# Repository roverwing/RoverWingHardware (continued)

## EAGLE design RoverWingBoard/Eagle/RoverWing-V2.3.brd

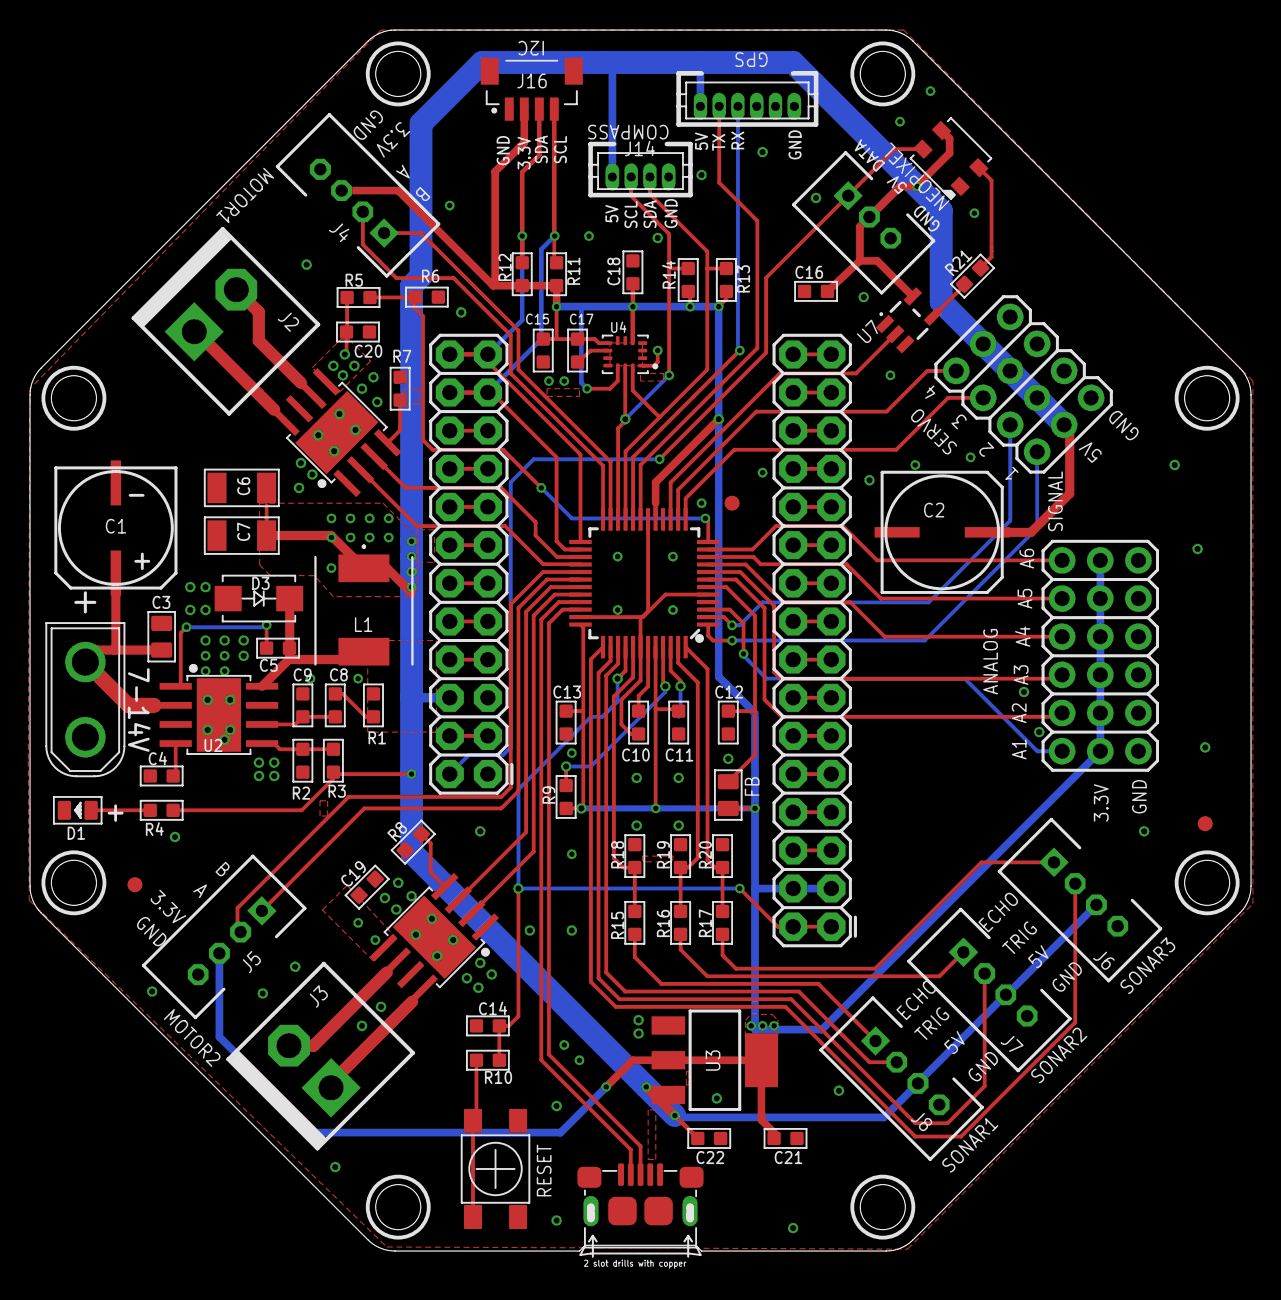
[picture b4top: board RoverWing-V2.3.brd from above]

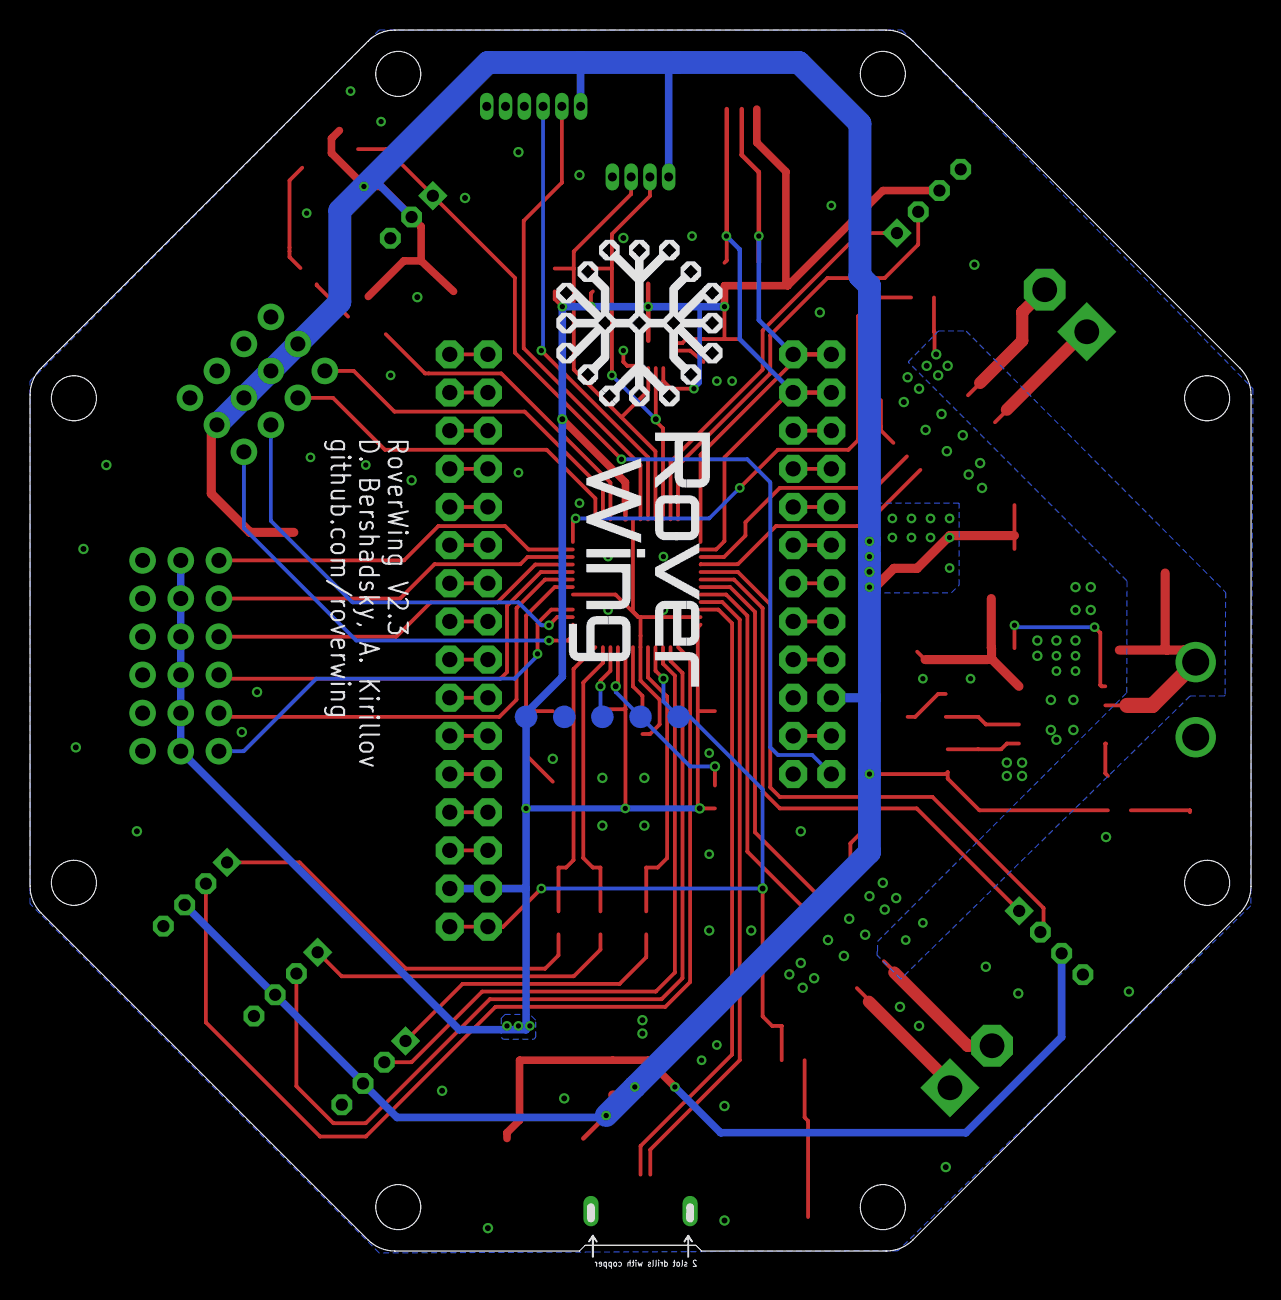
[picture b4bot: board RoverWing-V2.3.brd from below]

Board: 2 copper layers, 81.3 x 81.3 mm, 91 parts (5 on the bottom side), 84 nets.

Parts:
C1, C2: 220uF; CAP-8X10.5
C3: 10uF; 0805
C4, C18: 10nF; 0603
C5, C11, C12, C13, C14, C15, C16, C19, C20: 100nF; 0603
C6, C7: 47uF; 1206
C8, C17: 2.2nF; 0603
C9: 22pF; 0603
C10, C21, C22: 1uF; 0603
D1: GREEN; LED-0805
D2: LED3535
D3: CDBA540-HF; SMA-DO214AC
FB: 330R-1500MA; 0805
FRAME1, FRAME2: FRAME-LETTERNO_PACKAGE; DUMMY
J1: XT30UPB-M
J2, J3: HEADER-VH; B2P-VH
J4, J5, J6, J7, J8: HEADER-PH-4P; B4B-PH-K
J9: HEADER-PH-3P; B3B-PH-K
J10: HEADER-3X04; 3X04
J11: HEADER-3X06ANGLE; 3X06
J12: HEADER-2X16; 2X16
J13: HEADER-2X12; 2X12
J14: DF13-4P-1.25DSA
J15: DF13-6P-1.25DSA
J16: HEADER-SH-4P; CONN_BM04B-SRSS-TB(LF)(SN)
L1: 4.7uH; IND_TDK_7.1X6.5
R1, R5: 37.4K; 0603
R2, R11, R12, R13, R14, R18, R19, R20: 1.8K; 0603
R3, R6: 9.53K; 0603
R4, R9, R10, R15, R16, R17: 1K; 0603
R7, R8: 22K; 0603
R21: 330; 0603
SW1: SW-TACTILE-4.5X4.5_SMD; TL3305
TP1, TP2, TP3, TP4, TP5: TPTP15R; TP15R
U1: ATSAMD21G; TQFP-48-EDITED
U2: TPS54531; HSOP8
U3: PMIC-AZ1117EH-3.3; SOT223
U4: ICM-42605; PQFN50P300X250X97-14N
U5, U6: DRV8871; HSOP8
U7: 74AHCT1G125DBV; SOT23-5
U$3, U$4, U$14, U$15, U$24, U$25, U$26, U$27: MOUNTINGHOLE3.0_NPH; MOUNTINGHOLE_3.0_NPH
U$11, U$13, U$17: FIDUCIAL; FIDUCIAL_1MM
USB1: MICRO-USB-SMD-B-(10118193-0001LF); MICRO-USB5+6P-SMD-0.65-B

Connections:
3.3V: C11.2, C13.2, C15.2, C17.2, C18.1, C21.2, FB.2, J4.3, J5.3, J11.2, J11.5, J11.8, J11.11, J11.14, J11.17, J12.3, J12.4, J16.2, R9.1, R11.1, R12.1, R13.1, R14.1, TP5.TP, U1.17, U1.36, U1.44, U3.2, U3.4, U4.5, U4.8, U4.12
5V: C2.+, C6.2, C7.2, C16.2, C22.2, D2.3, J6.3, J7.3, J8.3, J9.2, J10.2, J10.5, J10.8, J10.11, J13.6, J14.P$1, J15.P$1, L1.1, R3.2, R4.2, U3.3, U7.5
12V: C1.+, C3.2, C19.1, C20.1, J1.+, R5.2, U2.2, U5.5, U6.5
!RESET: C14.1, J12.1, J12.2, R10.2, TP1.TP, U1.40
ANALOG1: J11.3, U1.3
ANALOG2: J11.6, U1.7
ANALOG3: J11.9, U1.8
ANALOG4: J11.12, U1.9
ANALOG5: J11.15, U1.10
ANALOG6: J11.18, U1.11
BOOT: C5.1, U2.1
D+: U1.34, USB1.3
D-: U1.33, USB1.2
ENC1A: J4.2, U1.24
ENC1B: J4.1, U1.23
ENC2A: J5.2, U1.29
ENC2B: J5.1, U1.30
GND: C1.-, C2.-, C3.1, C4.1, C6.1, C7.1, C9.1, C10.1, C11.1, C12.1, C13.1, C14.2, C15.1, C16.1, C17.1, C18.2, C19.2, C20.2, C21.1, C22.1, D1.-, D2.1, D3.A, J1.-, J4.4, J5.4, J6.4, J7.4, J8.4, J9.3, J10.1, J10.4, J10.7, J10.10, J11.1, J11.4, J11.7, J11.10, J11.13, J11.16, J12.7, J12.8, J14.P$4, J15.P$6, J16.1, R1.1, R2.1, R6.2, R7.2, R8.2, R18.2, R19.2, R20.2, SW1.2, SW1.3, TP4.TP, U1.5, U1.18, U1.35, U1.42, U2.7, U2.GND, U2.P$1, U2.P$2, U2.P$3, U2.P$4, U3.1, U4.1, U4.6, U4.7, U4.9, U5.1, U5.7, U5.GND, U5.P$1, U5.P$2, U5.P$3, U5.P$4, U6.1, U6.7, U6.GND, U6.P$1, U6.P$2, U6.P$3, U6.P$4, U7.1, U7.3, USB1.5, USB1.S1, USB1.S2, USB1.S3, USB1.S4, USB1.S5, USB1.S6
MOTOR1A: U1.27, U5.3
MOTOR1B: U1.28, U5.2
MOTOR2A: U1.31, U6.3
MOTOR2B: U1.32, U6.2
unnamed: J3.1, U6.8
unnamed: J3.2, U6.6
unnamed: J2.1, U5.8
unnamed: R21.2, U7.4
unnamed: J13.3, J13.4
unnamed: D2.2, R21.1
unnamed: J8.1, R15.1
unnamed: J13.7, J13.8
unnamed: J6.1, R17.1
unnamed: R10.1, SW1.1, SW1.4
unnamed: J13.9, J13.10
unnamed: C10.2, U1.43
unnamed: J13.11, J13.12
unnamed: J2.2, U5.6
unnamed: D1.+, R4.1
unnamed: J13.15, J13.16
unnamed: R7.1, U5.4
unnamed: R8.1, U6.4
unnamed: J7.1, R16.1
unnamed: J13.13, J13.14
unnamed: C5.2, D3.K, L1.2, U2.8
unnamed: C4.2, U2.4
unnamed: J12.5, J12.6
unnamed: C8.1, R1.2
unnamed: C8.2, C9.2, U2.6
unnamed: J13.17, J13.18
unnamed: J13.19, J13.20
unnamed: J12.9, J12.10
unnamed: J12.11, J12.12
unnamed: J12.13, J12.14
unnamed: J12.15, J12.16
unnamed: J12.17, J12.18
unnamed: J12.19, J12.20
unnamed: J12.21, J12.22
unnamed: J12.23, J12.24
unnamed: J12.25, J12.26
unnamed: J12.27, J12.28
unnamed: J12.29, J12.30
unnamed: J12.31, J12.32
NEOPIXEL: U1.15, U7.2
NEOPIXEL_OUT: D2.4, J9.1, J13.2
RX: J15.P$3, U1.20
SCL1: J13.21, J13.22, J16.4, R11.2, U1.26
SCL2: J14.P$2, R14.2, U1.22, U4.13
SDA1: J13.23, J13.24, J16.3, R12.2, U1.25
SDA2: J14.P$3, R13.2, U1.21, U4.14
SERVO1: J10.3, U1.1
SERVO2: J10.6, U1.2
SERVO3: J10.9, U1.13
SERVO4: J10.12, U1.14
SONAR1ECHO: R15.2, R18.1, U1.41
SONAR1TRIG: J8.2, U1.39
SONAR2ECHO: R16.2, R19.1, U1.47
SONAR2TRIG: J7.2, U1.38
SONAR3ECHO: R17.2, R20.1, U1.48
SONAR3TRIG: J6.2, U1.37
SWCLK: R9.2, TP2.TP, U1.45
SWDIO: TP3.TP, U1.46
TX: J15.P$2, U1.19
VDDANA: C12.2, FB.1, U1.6
VSENSE: R5.1, R6.1, U1.12
VSENSE2: R2.2, R3.1, U2.5

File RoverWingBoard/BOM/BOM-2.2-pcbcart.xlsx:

Manufacturer | Manufacturer Part Number | Designator | Qty | Description | Value | Package | Top/bottom | Type | Points | Total points | Flexibility
MICROCHIP TECHNOLOGY | ATSAMD21G18A-AU | U1 | 1 | SAMD21G MCU | ATSAMD21G | TQFP-48 | top | SMD | 48 | 48
TEXAS INSTRUMENTS | TPS54531 | U2 | 1 | Switching Voltage Regulator | TPS54531 | HSOP8 | top | SMD | 8 | 8
DIODES INC | AZ1117EH-3.3TRG1 | U3 | 1 | LDO VOLTAGE REGULATOR | PMIC-AZ1117EH-3.3 | SOT223 | top | SMD | 4 | 4
TDK INVENSENSE | ICM-42605 | U4 | 1 | Single-Interface MotionTracking device The ICM-42605 is a 6-axis MotionTracking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 | ICM-42605 | PQFN50P300X250X97-14N | top | SMD | 14 | 14
TEXAS INSTRUMENTS | DRV8871DDAR | U5, U6 | 2 | DRV8871 - 3.6A PWM Motor Driver | DRV8871 | HSOP8 | top | SMD | 8 | 16
TEXAS INSTRUMENTS | SN74AHCT1G125DBVR | U7 | 1 | Single Bus Buffer Gate with 3-State Output | 74AHCT1G125DBV | SOT23-5 | top | SMD | 5 | 5
AMPHENOL ICC | 10118193-0001LF | USB1 | 1 | Micro USB connector, 5 pin | MICRO-USB-SMD-B-(10118193-0001LF) | MICRO-USB5+6P-SMD-0.65-B | top | SMD | 5 | 5
BRIGHT | TSA453G38-250 | SW1 | 1 | Tactile Switch, 4.5*4.5 mm SMD | SW-TACTILE-4.5X4.5_SMD | TL3305 | top | SMD | 4 | 4
LITE-ON | LTST-C170KGKT | D1 | 1 | SMD LED, 0805 | GREEN | LED-0805 | top | SMD | 2 | 2
WORLDSEMI | WS2812B-MINI | D2 | 1 | SMART LED, 3.5MM |  | LED3535 | top | SMD | 4 | 4
COMCHIP TECHNOLOGIES | CDBA540-HF | D3 | 1 | Schottky diode, 40V, 5A, DO-214 | CDBA540-HF | SMA-DO214AC | top | SMD | 2 | 2
MURATA ELECTRONICS | BLM21PG331SN1D | FB | 1 | Ferrite Bead | 330R-1500MA | 0805 | top | SMD | 2 | 2
TDK | SPM6530T-4R7M | L1 | 1 | Power inductor, SMD, 4.7uH, 5.2A | 4.7uH | IND_TDK_7.1X6.5 | top | SMD | 2 | 2
SEMTECH | CK1V221MCRF10 | C1, C2 | 2 | AL CAPACITOR, SMD | 220uF | CAP-8X10.5 | top | SMD | 2 | 4
Taiyo Yuden | TMK212BBJ106KG-T | C3 | 1 | CAP CERAMIC, 25V, SMD | 10uF | 0805 | top | SMD | 2 | 2 | yes
Taiyo Yuden | UMK107B103KAHT | C4, C18 | 2 | CAP CERAMIC, 10V, SMD | 10nF | 0603 | top | SMD | 2 | 4 | yes
Taiyo Yuden | UMK107B104KAHT | C5, C11, C12, C13, C14, C15, C16, C19, C20 | 9 | CAP CERAMIC, 10V, SMD | 100nF | 0603 | top | SMD | 2 | 18 | yes
Taiyo Yuden | LMK316BJ476ML-T | C6, C7 | 2 | CAP CERAMIC, 10V, SMD | 47uF | 1206 | top | SMD | 2 | 4 | yes
YAGEO | CC0603KRX7R9BB222 | C8, C17 | 2 | CAP CERAMIC,50V, SMD | 2.2nF | 0603 | top | SMD | 2 | 4 | yes
YAGEO | CC0603JRNPO9BN220 | C9 | 1 | CAP CERAMIC, 50V, SMD | 22pF | 0603 | top | SMD | 2 | 2 | yes
Taiyo Yuden | TMK107BJ105KA-T | C10, C21, C22 | 3 | CAP CERAMIC, 25V, SMD | 1uF | 0603 | top | SMD | 2 | 6 | yes
YAGEO | RC0603FR-0737K4L | R1, R5 | 2 | SMD RESISTOR, 1%, 1/10W, 0603 | 37.4K | 0603 | top | SMD | 2 | 4 | yes
YAGEO | RC0603JR-071K8L | R2, R11, R12, R13, R14, R18, R19, R20 | 8 | SMD RESISTOR, 1%, 1/10W, 0603 | 1.8K | 0603 | top | SMD | 2 | 16 | yes
YAGEO | RC0603FR-079K53L | R3, R6 | 2 | SMD RESISTOR, 1%, 1/10W, 0603 | 9.53K | 0603 | top | SMD | 2 | 4 | yes
YAGEO | RC0603JR-071KL | R4, R9, R10, R15, R16, R17 | 6 | SMD RESISTOR, 1%, 1/10W, 0603 | 1K | 0603 | top | SMD | 2 | 12 | yes
YAGEO | RC0805FR-0722KL | R7, R8 | 2 | SMD RESISTOR, 5%, 1/10W, 0603 | 22K | 0603 | top | SMD | 2 | 4 | yes
YAGEO | RC0603JR-07330RL | R21 | 1 | SMD RESISTOR, 5%, 1/10W, 0603 | 330 | 0603 | top | SMD | 2 | 2 | yes
AMASS | XT30UPB-M | J1 | 1 | AMASS XT30 connector | XT30UPB-M | XT30UPB-M | top | PTH | 2 | 2
JST | B2P-VH(LF)(SN) | J2, J3 | 2 | HEADER - JST VH, 2P | HEADER-VH | B2P-VH | top | PTH | 2 | 4
JST | B4B-PH-K-S(LF)(SN) | J4, J5, J6, J7, J8 | 5 | HEADER, JST PH, 4POS, THROUGH HOLE, STRAIGHT | HEADER-PH-4P | B4B-PH-K | top | PTH | 4 | 20
JST | B3B-PH-K-S(LF)(SN) | J9 | 1 | HEADER, JST PH, 3POS, THROUGH HOLE, STRAIGHT | HEADER-PH-3P | B3B-PH-K | top | PTH | 3 | 3
SAMTEC | TSW-104-08-T-T-RA | J10 | 1 | HEADER - 3x4, 0.1" PITCH, MALE, RIGHT ANGLE | HEADER-3X04 | 3X04 | top | PTH | 12 | 12 | yes
SAMTEC | TSW-106-10-T-T-RA | J11 | 1 | HEADER - 3x6, 0.1" PITCH, MALE, RIGHT ANGLE | HEADER-3X06 | 3X06 | top | PTH | 18 | 18 | yes
CONNFLY ELEC | DS1023-2*16SF11 | J12 | 1 | HEADER - 2x16, 0.1" PITCH, FEMALE | HEADER-2X16 | 2X16 | top | PTH | 32 | 32 | yes
CONNFLY ELEC | DS1023-2*12SF11 | J13 | 1 | HEADER, 2x12, 0.1" PITCH, FEMALE | HEADER-2X12 | 2X12 | top | PTH | 24 | 24 | yes
HIROSE | DF13-4P-1.25DSA | J14 | 1 | HEADER - DF13-4P | DF13-4P-1.25DSA | DF13-4P-1.25DSA | top | PTH | 4 | 4
HIROSE | DF13-6P-1.25DSA | J15 | 1 | HEADER - DF13-6P | DF13-6P-1.25DSA | DF13-6P-1.25DSA | top | PTH | 6 | 6
JST | BM04B-SRSS-TB_LF__SN_ | J16 | 1 | HEADER, JST SH 4POS SMD STRAIGHT | HEADER-SH-4P | CONN_BM04B-SRSS-TB(LF)(SN) | top | SMD | 4 | 4
 |  | Totals |  |  |  |  |  |  |  | 331

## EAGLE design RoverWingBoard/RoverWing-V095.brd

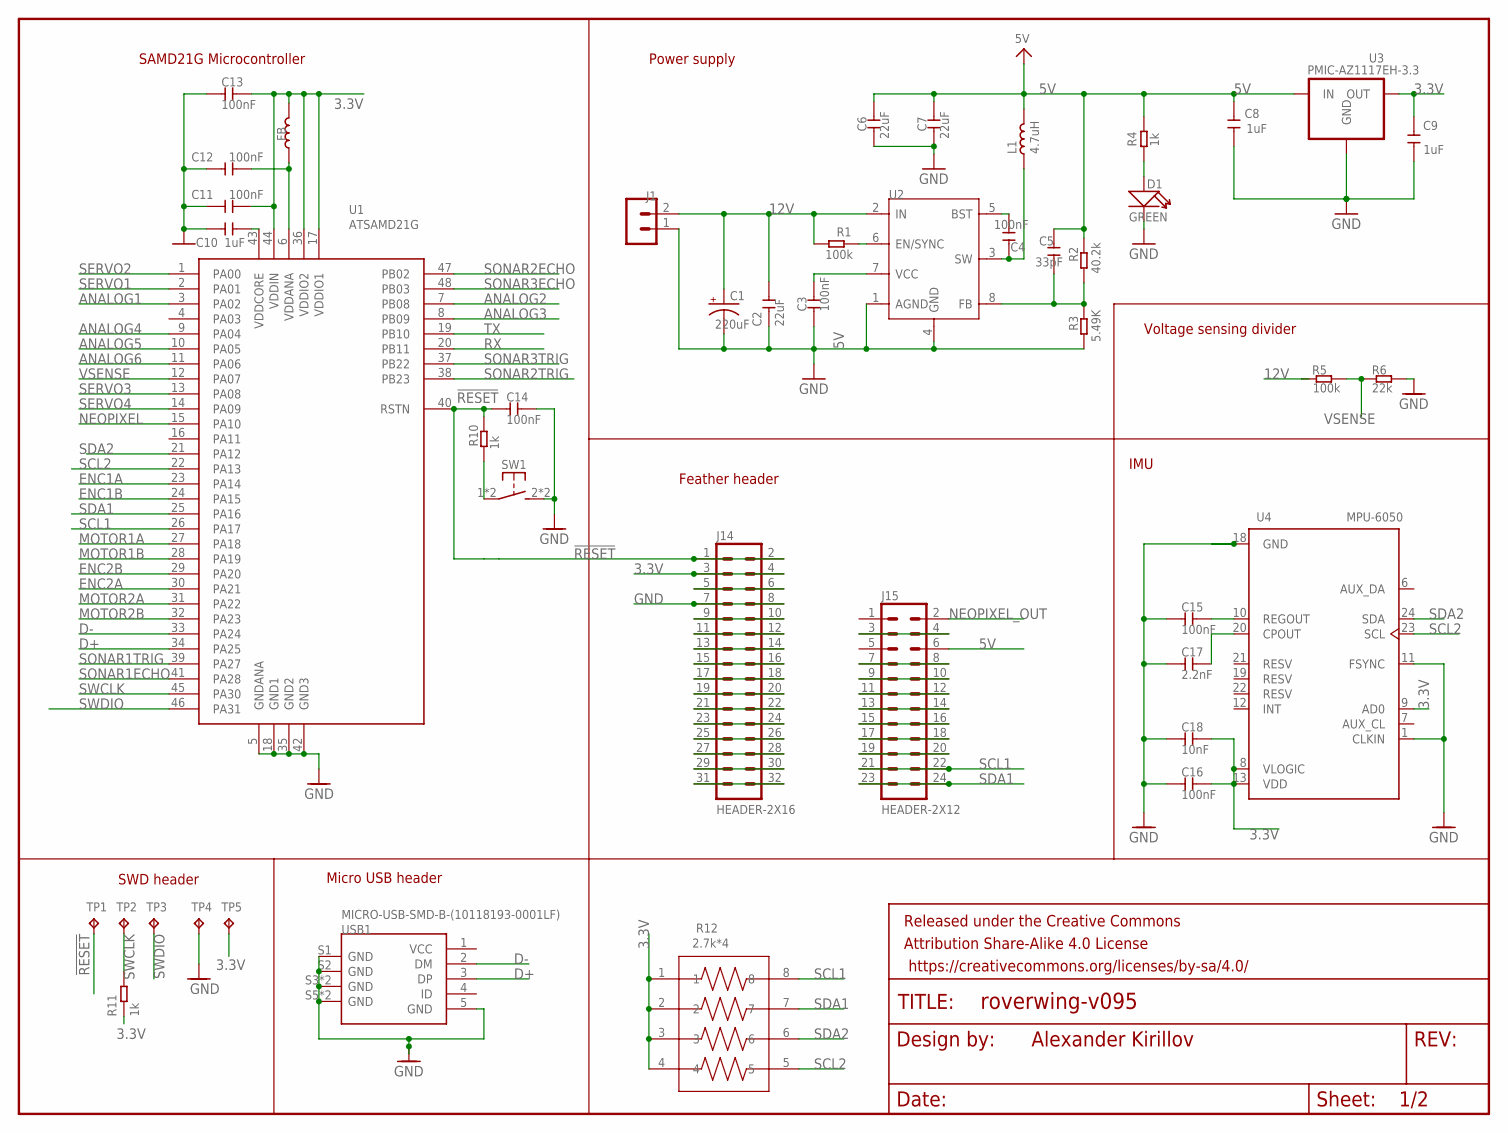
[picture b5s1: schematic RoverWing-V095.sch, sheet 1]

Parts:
C1: 220uF; CAP-8X10.5
C2, C6, C7: 22uF; 0805
C3, C4, C11, C12, C13, C14, C15, C16: 100nF; 0805
C5: 33pF; 0805
C8, C9, C10: 1uF; 0805
C17: 2.2nF; 0805
C18: 10nF; 0805
D1: GREEN; LED-0805
FB: 330R-1500MA; 0805
FRAME2: FRAME-LETTERNO_PACKAGE; DUMMY
J1: HEADER-VH; B2P-VH
J14: HEADER-2X16; 2X16
J15: HEADER-2X12; 2X12
L1: 4.7uH; IND_TDK_7.1X6.5
R1, R5: 100k; 0805
R2: 40.2k; 0805
R3: 5.49K; 0805
R4, R10, R11: 1k; 0805
R6: 22k; 0805
R12: 2.7k*4; 0603*4
SW1: SW-TACTILE-4.5X4.5_SMD; TL3305
TP1, TP2, TP3, TP4, TP5: TPTP15R; TP15R
U1: ATSAMD21G; TQFP-48-EDITED
U2: MP2225; SOT-23-8
U3: PMIC-AZ1117EH-3.3; SOT223
U4: MPU-6050; QFN50P400X400X95-24N
USB1: MICRO-USB-SMD-B-(10118193-0001LF); MICRO-USB5+6P-SMD-0.65-B

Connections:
3.3V: C9.2, C11.2, C13.2, C16.2, C18.2, FB.2, J14.3, J14.4, R11.1, R12.1, R12.2, R12.3, R12.4, TP5.TP, U1.17 (VDDIO1), U1.36 (VDDIO2), U1.44 (VDDIN), U3.2 (OUT), U3.4 (OUT), U4.8 (VLOGIC), U4.9 (AD0), U4.13 (VDD); also elsewhere on the board
5V: C5.2, C6.2, C7.2, C8.2, J15.6, L1.2, R2.1, R4.2, U3.3 (IN); also elsewhere on the board
12V: C1.+, C2.2, J1.2, R1.2, R5.2, U2.2 (IN); also elsewhere on the board
!RESET: C14.1, J14.1, J14.2, R10.2, TP1.TP, U1.40 (RSTN)
ANALOG1: U1.3 (PA02); also elsewhere on the board
ANALOG2: U1.7 (PB08); also elsewhere on the board
ANALOG3: U1.8 (PB09); also elsewhere on the board
ANALOG4: U1.9 (PA04); also elsewhere on the board
ANALOG5: U1.10 (PA05); also elsewhere on the board
ANALOG6: U1.11 (PA06); also elsewhere on the board
BST: C4.1, U2.5 (BST)
D+: U1.34 (PA25), USB1.3 (DP)
D-: U1.33 (PA24), USB1.2 (DM)
ENC1A: U1.23 (PA14); also elsewhere on the board
ENC1B: U1.24 (PA15); also elsewhere on the board
ENC2A: U1.30 (PA21); also elsewhere on the board
ENC2B: U1.29 (PA20); also elsewhere on the board
FB: C5.1, R2.2, R3.1, U2.8 (FB)
GND: C1.-, C2.1, C3.1, C6.1, C7.1, C8.1, C9.1, C10.1, C11.1, C12.1, C13.1, C14.2, C15.1, C16.1, C17.1, C18.1, D1.-, J1.1, J14.7, J14.8, R3.2, R6.2, SW1.2 (S1), SW1.3 (S1), TP4.TP, U1.5 (GNDANA), U1.18 (GND1), U1.35 (GND2), U1.42 (GND3), U2.1 (AGND), U2.4 (GND), U3.1 (GND), U4.1 (CLKIN), U4.11 (FSYNC), U4.18 (GND), USB1.5 (GND), USB1.S1 (GND), USB1.S2 (GND), USB1.S3 (GND), USB1.S4 (GND), USB1.S5 (GND), USB1.S6 (GND); also elsewhere on the board
MOTOR1A: U1.27 (PA18); also elsewhere on the board
MOTOR1B: U1.28 (PA19); also elsewhere on the board
MOTOR2A: U1.31 (PA22); also elsewhere on the board
MOTOR2B: U1.32 (PA23); also elsewhere on the board
unnamed: C17.2, U4.20 (CPOUT)
unnamed: J15.3, J15.4
unnamed: C15.2, U4.10 (REGOUT)
unnamed: J15.7, J15.8
unnamed: R10.1, SW1.1, SW1.4 (P1)
unnamed: J15.9, J15.10
unnamed: C10.2, U1.43 (VDDCORE)
unnamed: J15.11, J15.12
unnamed: D1.+, R4.1
unnamed: J15.15, J15.16
unnamed: J15.13, J15.14
unnamed: R1.1, U2.6 (EN/SYNC)
unnamed: C3.2, U2.7 (VCC)
unnamed: J14.5, J14.6
unnamed: J15.17, J15.18
unnamed: J15.19, J15.20
unnamed: J14.9, J14.10
unnamed: J14.11, J14.12
unnamed: J14.13, J14.14
unnamed: J14.15, J14.16
unnamed: J14.17, J14.18
unnamed: J14.19, J14.20
unnamed: J14.21, J14.22
unnamed: J14.23, J14.24
unnamed: J14.25, J14.26
unnamed: J14.27, J14.28
unnamed: J14.29, J14.30
unnamed: J14.31, J14.32
NEOPIXEL: U1.15 (PA10); also elsewhere on the board
NEOPIXEL_OUT: J15.2; also elsewhere on the board
RX: U1.20 (PB11); also elsewhere on the board
SCL1: J15.21, J15.22, R12.8, U1.26 (PA17); also elsewhere on the board
SCL2: R12.5, U1.22 (PA13), U4.23 (SCL); also elsewhere on the board
SDA1: J15.23, J15.24, R12.7, U1.25 (PA16); also elsewhere on the board
SDA2: R12.6, U1.21 (PA12), U4.24 (SDA); also elsewhere on the board
SERVO1: U1.2 (PA01); also elsewhere on the board
SERVO2: U1.1 (PA00); also elsewhere on the board
SERVO3: U1.13 (PA08); also elsewhere on the board
SERVO4: U1.14 (PA09); also elsewhere on the board
SONAR1ECHO: U1.41 (PA28); also elsewhere on the board
SONAR1TRIG: U1.39 (PA27); also elsewhere on the board
SONAR2ECHO: U1.47 (PB02); also elsewhere on the board
SONAR2TRIG: U1.38 (PB23); also elsewhere on the board
SONAR3ECHO: U1.48 (PB03); also elsewhere on the board
SONAR3TRIG: U1.37 (PB22); also elsewhere on the board
SW: C4.2, L1.1, U2.3 (SW)
SWCLK: R11.2, TP2.TP, U1.45 (PA30)
SWDIO: TP3.TP, U1.46 (PA31)
TX: U1.19 (PB10); also elsewhere on the board
VDDANA: C12.2, FB.1, U1.6 (VDDANA)
VSENSE: R5.1, R6.1, U1.12 (PA07)

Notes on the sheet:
SWD header
Alexander Kirillov
SAMD21G Microcontroller
Micro USB header
Power supply
Feather header
IMU
Voltage sensing divider

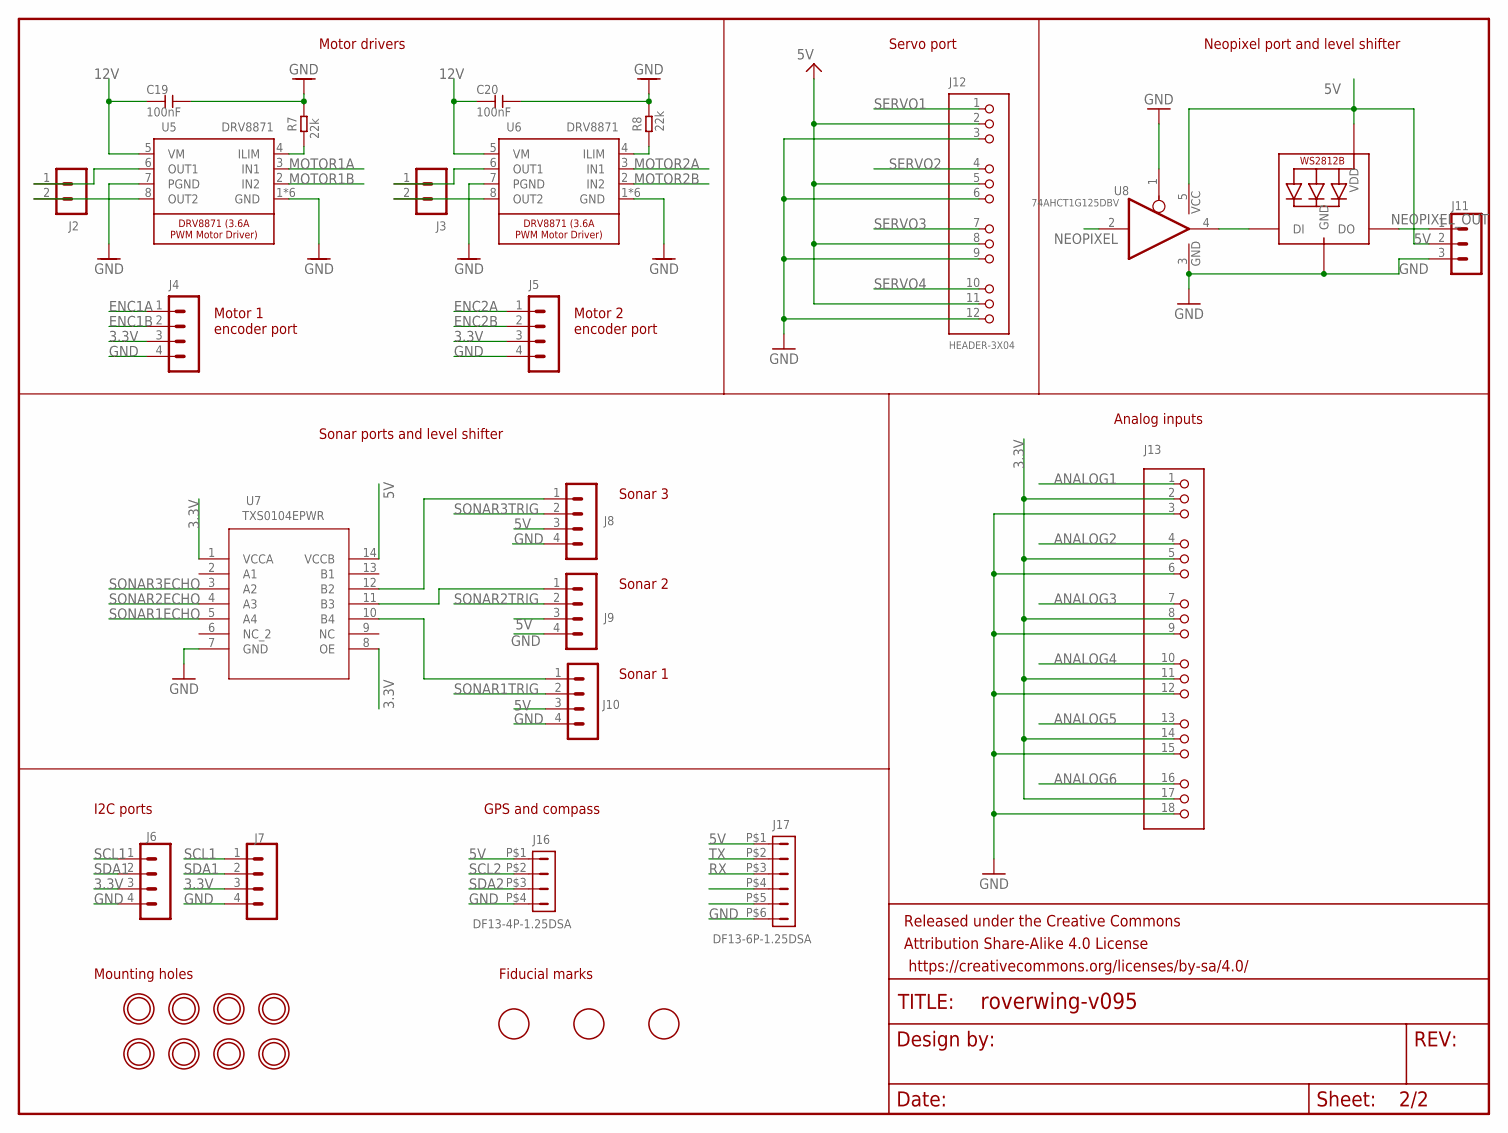
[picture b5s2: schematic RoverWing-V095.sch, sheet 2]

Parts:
C19, C20: 100nF; 0805
FRAME1: FRAME-LETTERNO_PACKAGE; DUMMY
J2, J3: HEADER-VH; B2P-VH
J4, J5, J6, J7, J8, J9, J10: HEADER-PH-4P; B4B-PH-K
J11: HEADER-PH-3P; B3B-PH-K
J12: HEADER-3X04; 3X04
J13: HEADER-3X06"; 3X06
J16: DF13-4P-1.25DSA
J17: DF13-6P-1.25DSA
LED1: WS2812B3535; LED3535
R7, R8: 22k; 0805
U5, U6: DRV8871; HSOP8
U7: TXS0104EPWR; PW14
U8: 74AHCT1G125DBV; SOT23-5
U$3, U$4, U$14, U$15, U$24, U$25, U$26, U$27: MOUNTINGHOLE3.0_NPH; MOUNTINGHOLE_3.0_NPH
U$11, U$13, U$17: FIDUCIAL; FIDUCIAL_1MM

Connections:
3.3V: J4.3, J5.3, J6.3, J7.3, J13.2, J13.5, J13.8, J13.11, J13.14, J13.17, U7.1 (VCCA), U7.8 (OE); also elsewhere on the board
5V: J8.3, J9.3, J10.3, J11.2, J12.2, J12.5, J12.8, J12.11, J16.P$1 (1), J17.P$1 (1), LED1.3 (VDD), U7.14 (VCCB), U8.5 (VCC); also elsewhere on the board
12V: C19.1, C20.1, U5.5 (VM), U6.5 (VM); also elsewhere on the board
ANALOG1: J13.1; also elsewhere on the board
ANALOG2: J13.4; also elsewhere on the board
ANALOG3: J13.7; also elsewhere on the board
ANALOG4: J13.10; also elsewhere on the board
ANALOG5: J13.13; also elsewhere on the board
ANALOG6: J13.16; also elsewhere on the board
ENC1A: J4.1; also elsewhere on the board
ENC1B: J4.2; also elsewhere on the board
ENC2A: J5.1; also elsewhere on the board
ENC2B: J5.2; also elsewhere on the board
GND: C19.2, C20.2, J4.4, J5.4, J6.4, J7.4, J8.4, J9.4, J10.4, J11.3, J12.3, J12.6, J12.9, J12.12, J13.3, J13.6, J13.9, J13.12, J13.15, J13.18, J16.P$4 (4), J17.P$6 (6), LED1.1 (GND), R7.2, R8.2, U5.1 (GND), U5.7 (PGND), U5.GND, U5.P$1 (GND), U5.P$2 (GND), U5.P$3 (GND), U5.P$4 (GND), U6.1 (GND), U6.7 (PGND), U6.GND, U6.P$1 (GND), U6.P$2 (GND), U6.P$3 (GND), U6.P$4 (GND), U7.7 (GND), U8.1 (OE), U8.3 (GND); also elsewhere on the board
MOTOR1A: U5.3 (IN1); also elsewhere on the board
MOTOR1B: U5.2 (IN2); also elsewhere on the board
MOTOR2A: U6.3 (IN1); also elsewhere on the board
MOTOR2B: U6.2 (IN2); also elsewhere on the board
unnamed: J3.2, U6.8 (OUT2)
unnamed: J3.1, U6.6 (OUT1)
unnamed: J2.2, U5.8 (OUT2)
unnamed: J10.1, U7.10 (B4)
unnamed: J8.1, U7.12 (B2)
unnamed: J2.1, U5.6 (OUT1)
unnamed: R7.1, U5.4 (ILIM)
unnamed: R8.1, U6.4 (ILIM)
unnamed: J9.1, U7.11 (B3)
unnamed: LED1.2 (DI), U8.4 (O)
NEOPIXEL: U8.2 (I); also elsewhere on the board
NEOPIXEL_OUT: J11.1, LED1.4 (DO); also elsewhere on the board
RX: J17.P$3 (3); also elsewhere on the board
SCL1: J6.1, J7.1; also elsewhere on the board
SCL2: J16.P$2 (2); also elsewhere on the board
SDA1: J6.2, J7.2; also elsewhere on the board
SDA2: J16.P$3 (3); also elsewhere on the board
SERVO1: J12.1; also elsewhere on the board
SERVO2: J12.4; also elsewhere on the board
SERVO3: J12.7; also elsewhere on the board
SERVO4: J12.10; also elsewhere on the board
SONAR1ECHO: U7.5 (A4); also elsewhere on the board
SONAR1TRIG: J10.2; also elsewhere on the board
SONAR2ECHO: U7.4 (A3); also elsewhere on the board
SONAR2TRIG: J9.2; also elsewhere on the board
SONAR3ECHO: U7.3 (A2); also elsewhere on the board
SONAR3TRIG: J8.2; also elsewhere on the board
TX: J17.P$2 (2); also elsewhere on the board

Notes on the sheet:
Motor drivers
Motor 2 encoder port
Motor 1 encoder port
Sonar ports and level shifter
Analog inputs
Neopixel port and level shifter
Servo port
Sonar 3
Sonar 2
Sonar 1
Mounting holes
Fiducial marks
I2C ports
GPS and compass
